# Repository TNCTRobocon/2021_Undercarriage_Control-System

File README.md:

# 2021_Undercarriage_Control-System
nucleo f446reを用いたロリコン制御足回り基板　発注済み　基本一生pullしないのでなんか変更加えたら言ってください

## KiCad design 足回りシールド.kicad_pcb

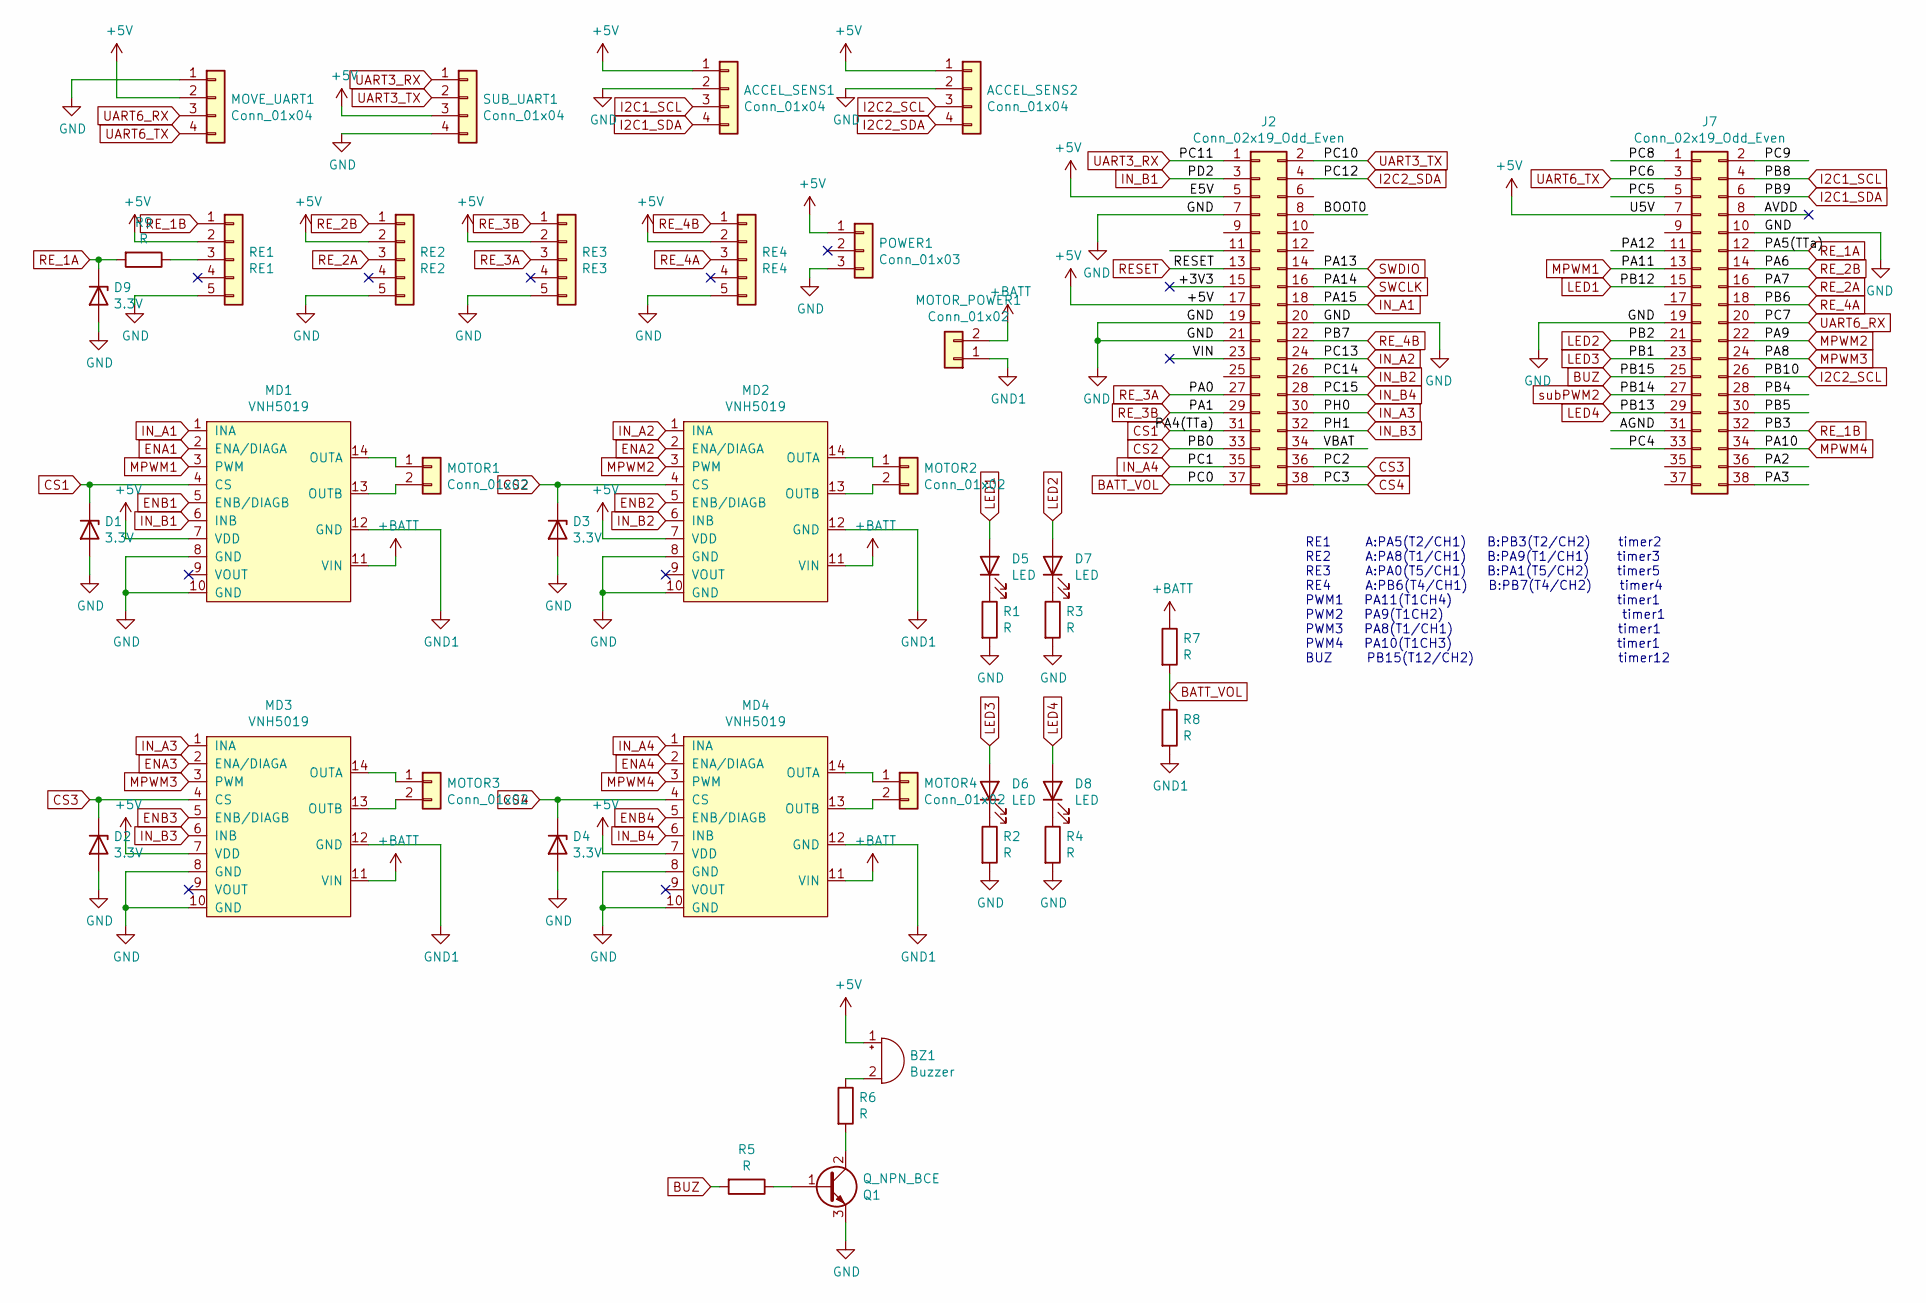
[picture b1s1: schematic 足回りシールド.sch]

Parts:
ACCEL_SENS1, ACCEL_SENS2: Conn_01x04; XA_04
BZ1: Buzzer; Buzzer_D14mm_H7mm_P10mm
D1, D2, D3, D4, D9: 3.3V; D_DO-34_SOD68_P7.62mm_Horizontal
D5, D6, D7, D8: LED; LED_Rectangular_W5.0mm_H2.0mm
J2, J7: Conn_02x19_Odd_Even; PinSocket_2x19_P2.54mm_Vertical
MD1, MD2, MD3, MD4: VNH5019
MOTOR1, MOTOR2, MOTOR3, MOTOR4: Conn_01x02; XT60
MOTOR_POWER1: Conn_01x02; XT60
MOVE_UART1: Conn_01x04; XA_04
POWER1: Conn_01x03; XA_03
Q1: Q_NPN_BCE; TO-92Flat
R1, R2, R3, R4, R5, R6, R7, R8, R9: R; R_Axial_DIN0207_L6.3mm_D2.5mm_P7.62mm_Horizontal
RE1: RE1; XA_05
RE2: RE2; XA_05
RE3: RE3; XA_05
RE4: RE4; XA_05
SUB_UART1: Conn_01x04; XA_04

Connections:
+5V: ACCEL_SENS1.1, ACCEL_SENS2.1, BZ1.1 (-), J2.5, J2.17, J7.7, MD1.7 (VDD), MD2.7 (VDD), MD3.7 (VDD), MD4.7 (VDD), MOVE_UART1.2, POWER1.1, RE1.2, RE2.2, RE3.2, RE4.2, SUB_UART1.3
+BATT: MD1.11 (VIN), MD2.11 (VIN), MD3.11 (VIN), MD4.11 (VIN), MOTOR_POWER1.2, R7.1
/+3V3: J2.15
/AGND: J7.31
/AVDD: J7.8
/BOOT0: J2.8
/PA2: J7.36
/PA3: J7.38
/PA12: J7.11
/PB4: J7.28
/PB5: J7.30
/PC4: J7.33
/PC5: J7.5
/PC8: J7.1
/PC9: J7.2
/VBAT: J2.34
/VIN: J2.23
BATT_VOL: J2.37, R7.2, R8.1
BUZ: J7.25, R5.2
CS1: D1.1 (K), J2.31, MD1.4 (CS)
CS2: D3.1 (K), J2.33, MD2.4 (CS)
CS3: D2.1 (K), J2.36, MD3.4 (CS)
CS4: D4.1 (K), J2.38, MD4.4 (CS)
ENA1: MD1.2 (ENA/DIAGA)
ENA2: MD2.2 (ENA/DIAGA)
ENA3: MD3.2 (ENA/DIAGA)
ENA4: MD4.2 (ENA/DIAGA)
ENB1: MD1.5 (ENB/DIAGB)
ENB2: MD2.5 (ENB/DIAGB)
ENB3: MD3.5 (ENB/DIAGB)
ENB4: MD4.5 (ENB/DIAGB)
GND: ACCEL_SENS1.2, ACCEL_SENS2.2, D1.2 (A), D2.2 (A), D3.2 (A), D4.2 (A), D9.2 (A), J2.7, J2.19, J2.20, J2.21, J7.10, J7.19, MD1.8 (GND), MD1.10 (GND), MD2.8 (GND), MD2.10 (GND), MD3.8 (GND), MD3.10 (GND), MD4.8 (GND), MD4.10 (GND), MOVE_UART1.1, POWER1.3, Q1.3 (E), R1.2, R2.2, R3.2, R4.2, RE1.5, RE2.5, RE3.5, RE4.5, SUB_UART1.4
GND1: MD1.12 (GND), MD2.12 (GND), MD3.12 (GND), MD4.12 (GND), MOTOR_POWER1.1, R8.2
I2C1_SCL: ACCEL_SENS1.3, J7.4
I2C1_SDA: ACCEL_SENS1.4, J7.6
I2C2_SCL: ACCEL_SENS2.3, J7.26
I2C2_SDA: ACCEL_SENS2.4, J2.4
IN_A1: J2.18, MD1.1 (INA)
IN_A2: J2.24, MD2.1 (INA)
IN_A3: J2.30, MD3.1 (INA)
IN_A4: J2.35, MD4.1 (INA)
IN_B1: J2.3, MD1.6 (INB)
IN_B2: J2.26, MD2.6 (INB)
IN_B3: J2.32, MD3.6 (INB)
IN_B4: J2.28, MD4.6 (INB)
LED1: D5.2 (A), J7.15
LED2: D7.2 (A), J7.21
LED3: D6.2 (A), J7.23
LED4: D8.2 (A), J7.29
MPWM1: J7.13, MD1.3 (PWM)
MPWM2: J7.22, MD2.3 (PWM)
MPWM3: J7.24, MD3.3 (PWM)
MPWM4: J7.34, MD4.3 (PWM)
unnamed: BZ1.2 (+), R6.1
unnamed: D5.1 (K), R1.1
unnamed: D6.1 (K), R2.1
unnamed: D7.1 (K), R3.1
unnamed: D8.1 (K), R4.1
unnamed: MD1.13 (OUTB), MOTOR1.2
unnamed: MD1.14 (OUTA), MOTOR1.1
unnamed: MD2.13 (OUTB), MOTOR2.2
unnamed: MD2.14 (OUTA), MOTOR2.1
unnamed: MD3.13 (OUTB), MOTOR3.2
unnamed: MD3.14 (OUTA), MOTOR3.1
unnamed: MD4.13 (OUTB), MOTOR4.2
unnamed: MD4.14 (OUTA), MOTOR4.1
unnamed: Q1.1 (B), R5.1
unnamed: Q1.2 (C), R6.2
unnamed: R9.1, RE1.3
RESET: J2.13
RE_1A: D9.1 (K), J7.12, R9.2
RE_1B: J7.32, RE1.1
RE_2A: J7.16, RE2.3
RE_2B: J7.14, RE2.1
RE_3A: J2.27, RE3.3
RE_3B: J2.29, RE3.1
RE_4A: J7.18, RE4.3
RE_4B: J2.22, RE4.1
SWCLK: J2.16
SWDIO: J2.14
UART3_RX: J2.1, SUB_UART1.1
UART3_TX: J2.2, SUB_UART1.2
UART6_RX: J7.20, MOVE_UART1.3
UART6_TX: J7.3, MOVE_UART1.4
subPWM2: J7.27

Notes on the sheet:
RE1 A:PA5(T2/CH1) B:PB3(T2/CH2) timer2 RE2 A:PA8(T1/CH1) B:PA9(T1/CH1) timer3 RE3 A:PA0(T5/CH1) B:PA1(T5/CH2) timer5 RE4 A:PB6(T4/CH1) B:PB7(T4/CH2) timer4 PWM1 PA11(T1CH4) timer1 PWM2 PA9(T1CH2) timer1 PWM3 PA8(T1/CH1) timer1 PWM4 PA10(T1CH3) timer1 BUZ PB15(T12/CH2) timer12

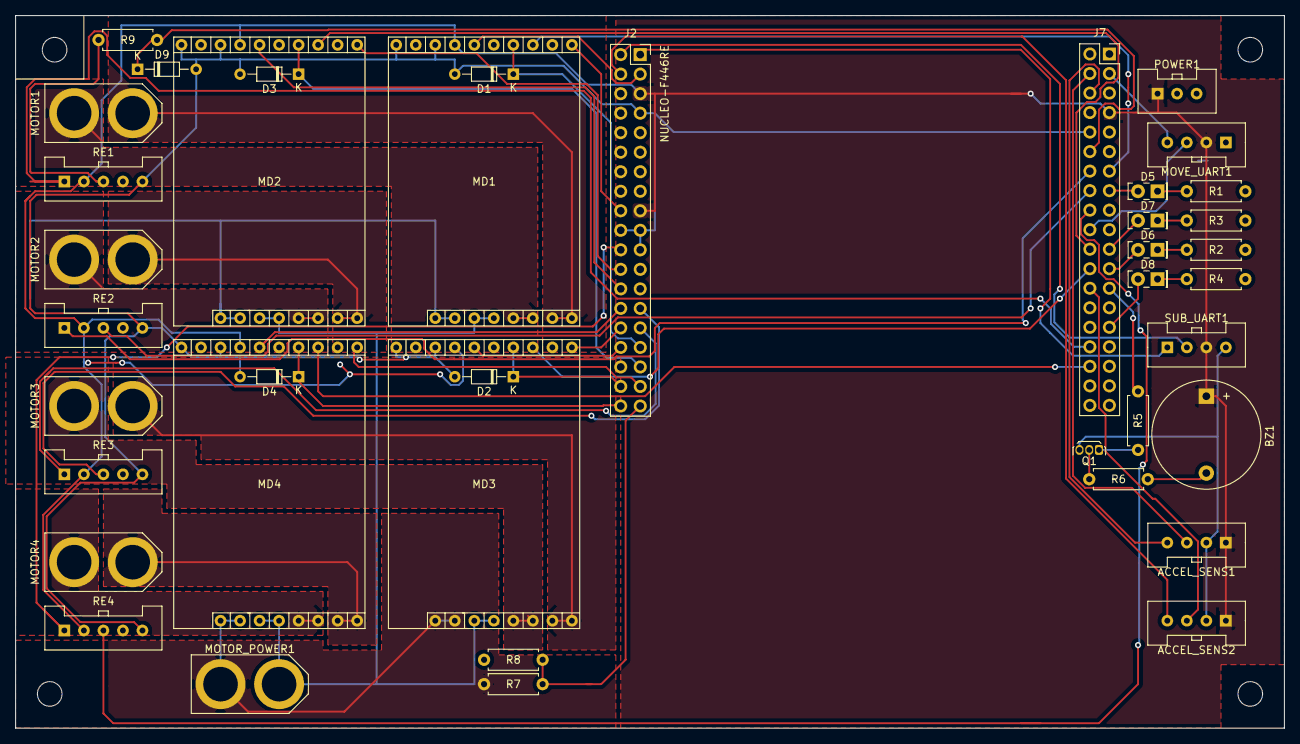
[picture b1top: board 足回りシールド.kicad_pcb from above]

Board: 2 copper layers, 165.1 x 92.7 mm, 44 parts (0 on the bottom side), 58 nets.

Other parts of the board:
M3, M3#2, M3#3, M3#4: MountingHole_3.2mm_M3

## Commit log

2021-06-27 ver1.1
